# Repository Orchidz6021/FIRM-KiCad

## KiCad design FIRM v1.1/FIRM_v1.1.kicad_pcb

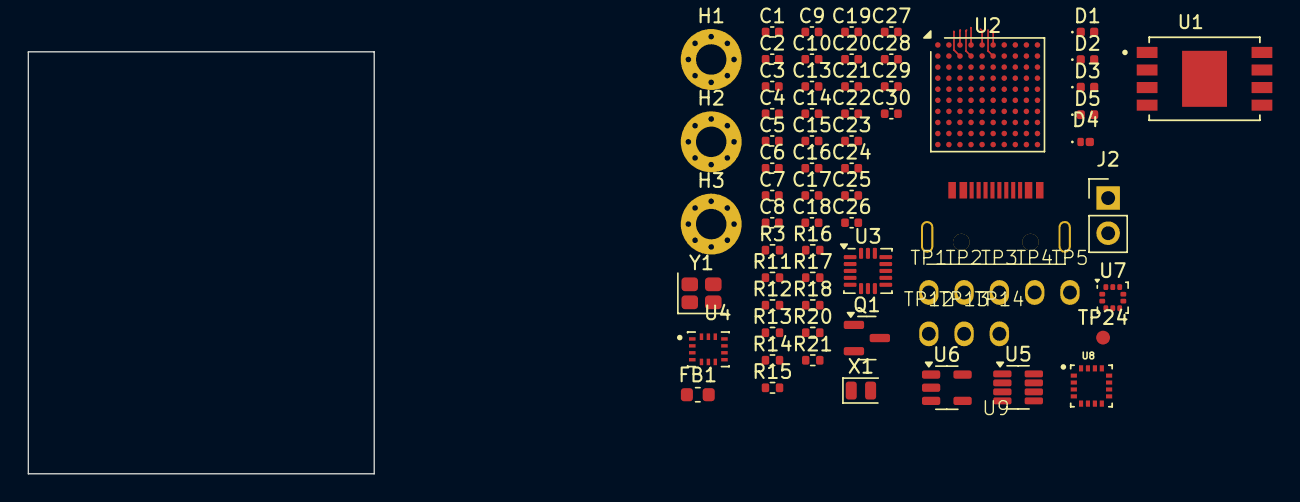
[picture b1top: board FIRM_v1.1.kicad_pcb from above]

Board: 8 copper layers, 25.0 x 30.5 mm, 70 parts (0 on the bottom side), 25 nets.

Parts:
C1, C3, C6, C8, C13, C15, C17, C19, C20, C21, C22, C23, C25, C27: 100n; C_0402_1005Metric
C2: 4u7; C_0402_1005Metric
C4, C7: 6p; C_0402_1005Metric
C5, C10: 14p; C_0402_1005Metric
C9, C14: 2u2; C_0402_1005Metric
C16: 10n; C_0402_1005Metric
C18, C29: 1u; C_0402_1005Metric
C24, C28, C30: 10u; C_0402_1005Metric
C26: 470p; C_0402_1005Metric
D1: LED_Blue; LED_0402_1005Metric
D2: LED_Yellow; LED_0402_1005Metric
D3: LED_Red; LED_0402_1005Metric
D4: D_Schottky; D_schottky_NSR05F30NXT5G
D5: LED_Green; LED_0402_1005Metric
FB1: 120 Ohms @ 100 MHz; L_0603_1608Metric
H1, H2, H3: MountingHole_Pad; MountingHole_2.2mm_M2_Pad_Via
J2: Conn_01x02_Pin; power_headers
Q1: IRLML6402; SOT-23
R3, R16: 100k; R_0402_1005Metric
R11, R12: 3k3; R_0402_1005Metric
R13: 1.2k; R_0402_1005Metric
R14, R15, R18: 1k2; R_0402_1005Metric
R17: 10m; R_0402_1005Metric
R20, R21: 5.1k; R_0402_1005Metric
TP1: PA0 Test Point; Testpoint_1.5x1.5mm_1.0mm
TP2: PA1 Test Point; Testpoint_1.5x1.5mm_1.0mm
TP3: PA2 Test Point; Testpoint_1.5x1.5mm_1.0mm
TP4: PA9 Test Point; Testpoint_1.5x1.5mm_1.0mm
TP5: PA10 Test Point; Testpoint_1.5x1.5mm_1.0mm
TP12: SWDIO Through-Hole; Testpoint_1.5x1.5mm_1.0mm
TP13: SWCLK Through-Hole; Testpoint_1.5x1.5mm_1.0mm
TP14: 3.3V Test Point; Testpoint_1.5x1.5mm_1.0mm
TP24: NRST Pad; smd_test_pads_1mm
U1: W25N04KVZEIR; IC_W25N04KVZEIR
U2: STM32H743VIHx; TFBGA-100_8x8mm_Layout10x10_P0.8mm
U3: ADXL371; Analog_LGA-16_3.25x3mm_P0.5mm_LayoutBorder3x5y
U4: IC_ICM-45686
U5: INA219AxDCN; SOT-23-8
U6: MIC5219-3.3YM5; SOT-23-5
U7: BMPFootprintNoSolderMask
U8: IC_MMC5983MA
U9: A-USBC-20F0-EA-GSR05
X1: 32.768khz; Crystal_ECS-.327-6-12RR-TR
Y1: 12 MHz; Crystal_ECS-120-10-36B2-CWY-TR

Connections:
+3.3V: C2.1, C3.1, C6.1, C8.1, C13.1, C15.1, C18.1, C19.2, C20.2, C21.1, C22.1, C23.2, C25.1, C27.2, C28.1, C29.1, FB1.2, R11.2, R12.2, R18.2, TP14.1, U2.B2 (VBAT), U2.D2 (VDD), U2.F5 (VDD), U2.F6 (VDD33_USB), U2.K1 (VDD), U3.1 (V_{DD_I/O}), U3.14 (V_{S}), U4.5 (VDDIO), U4.8 (VDD), U5.4 (VS), U6.5 (OUT), U7.1 (VDDIO), U7.10 (VDD), U8.2 (VDD), U8.13 (VDDIO)
/MISO2: U3.7 (MISO), U4.1 (AP_SDO/AP_AD0), U7.5 (SDO), U8.5 (SPI_SDO)
/MOSI2: U3.6 (MOSI), U4.14 (AP_SDA/APSDIO/APSDI), U7.4 (SDI), U8.16 (SDA/ SPI_SDI)
/SCK2: U3.4 (SCLK), U4.13 (AP_SCL/AP_SCLK), U7.2 (SCK), U8.1 (SCL/ SPI_SCK)
/USB_D+: U9.A6 (D+), U9.B6 (D+)
/USB_D-: U9.A7 (D-), U9.B7 (D-)
/VSENS_IN: D4.1 (K), Q1.2 (S), R17.1, U5.1 (IN+)
/VSENS_OUT: C24.1, R17.2, U5.2 (IN-), U6.1 (IN), U6.3 (EN)
GND: C1.2, C2.2, C3.2, C4.2, C5.2, C6.2, C7.2, C8.2, C9.2, C10.2, C13.2, C14.2, C15.2, C16.2, C17.2, C18.2, C19.1, C20.1, C21.2, C22.2, C23.1, C24.2, C25.2, C26.2, C27.1, C28.2, C29.2, C30.1, D1.1 (K), D2.1 (K), D3.1 (K), D5.1 (K), H1.1, H2.1, H3.1, J2.2, R3.2, R16.2, R20.2, R21.2, U3.12 (GND), U3.13 (GND), U3.16 (GND), U4.6 (GND), U5.3 (GND), U5.7 (A0), U5.8 (A1), U6.2 (GND), U7.3 (VSS), U7.8 (VSS), U7.9 (VSS), U8.9 (GND), U8.11 (GND), U9.A1 (GND), U9.B1 (GND), U9.S1 (SHIELD), Y1.2, Y1.4
unnamed: C4.1, X1.1
unnamed: C5.1, Y1.1
unnamed: C7.1, X1.2
unnamed: C10.1, Y1.3
unnamed: D1.2 (A), R13.1
unnamed: D2.2 (A), R14.1
unnamed: D3.2 (A), R15.1
unnamed: D5.2 (A), R18.1
unnamed: C16.1, C17.1, FB1.1, U2.H1 (VDDA)
unnamed: U2.C2 (VSS), U2.E4 (VSS), U2.E5 (VSS), U2.E6 (VSS), U2.J1 (VSS)
unnamed: C26.1, U6.4 (BP)
unnamed: C30.2, U8.10 (CAP)
unnamed: R20.1, U9.A5 (CC1)
unnamed: R21.1, U9.B5 (CC2)
VBAT: J2.1, Q1.3 (D)
VBUS: D4.2 (A), Q1.1 (G), R16.1, U9.A4 (VBUS), U9.B4 (VBUS)
